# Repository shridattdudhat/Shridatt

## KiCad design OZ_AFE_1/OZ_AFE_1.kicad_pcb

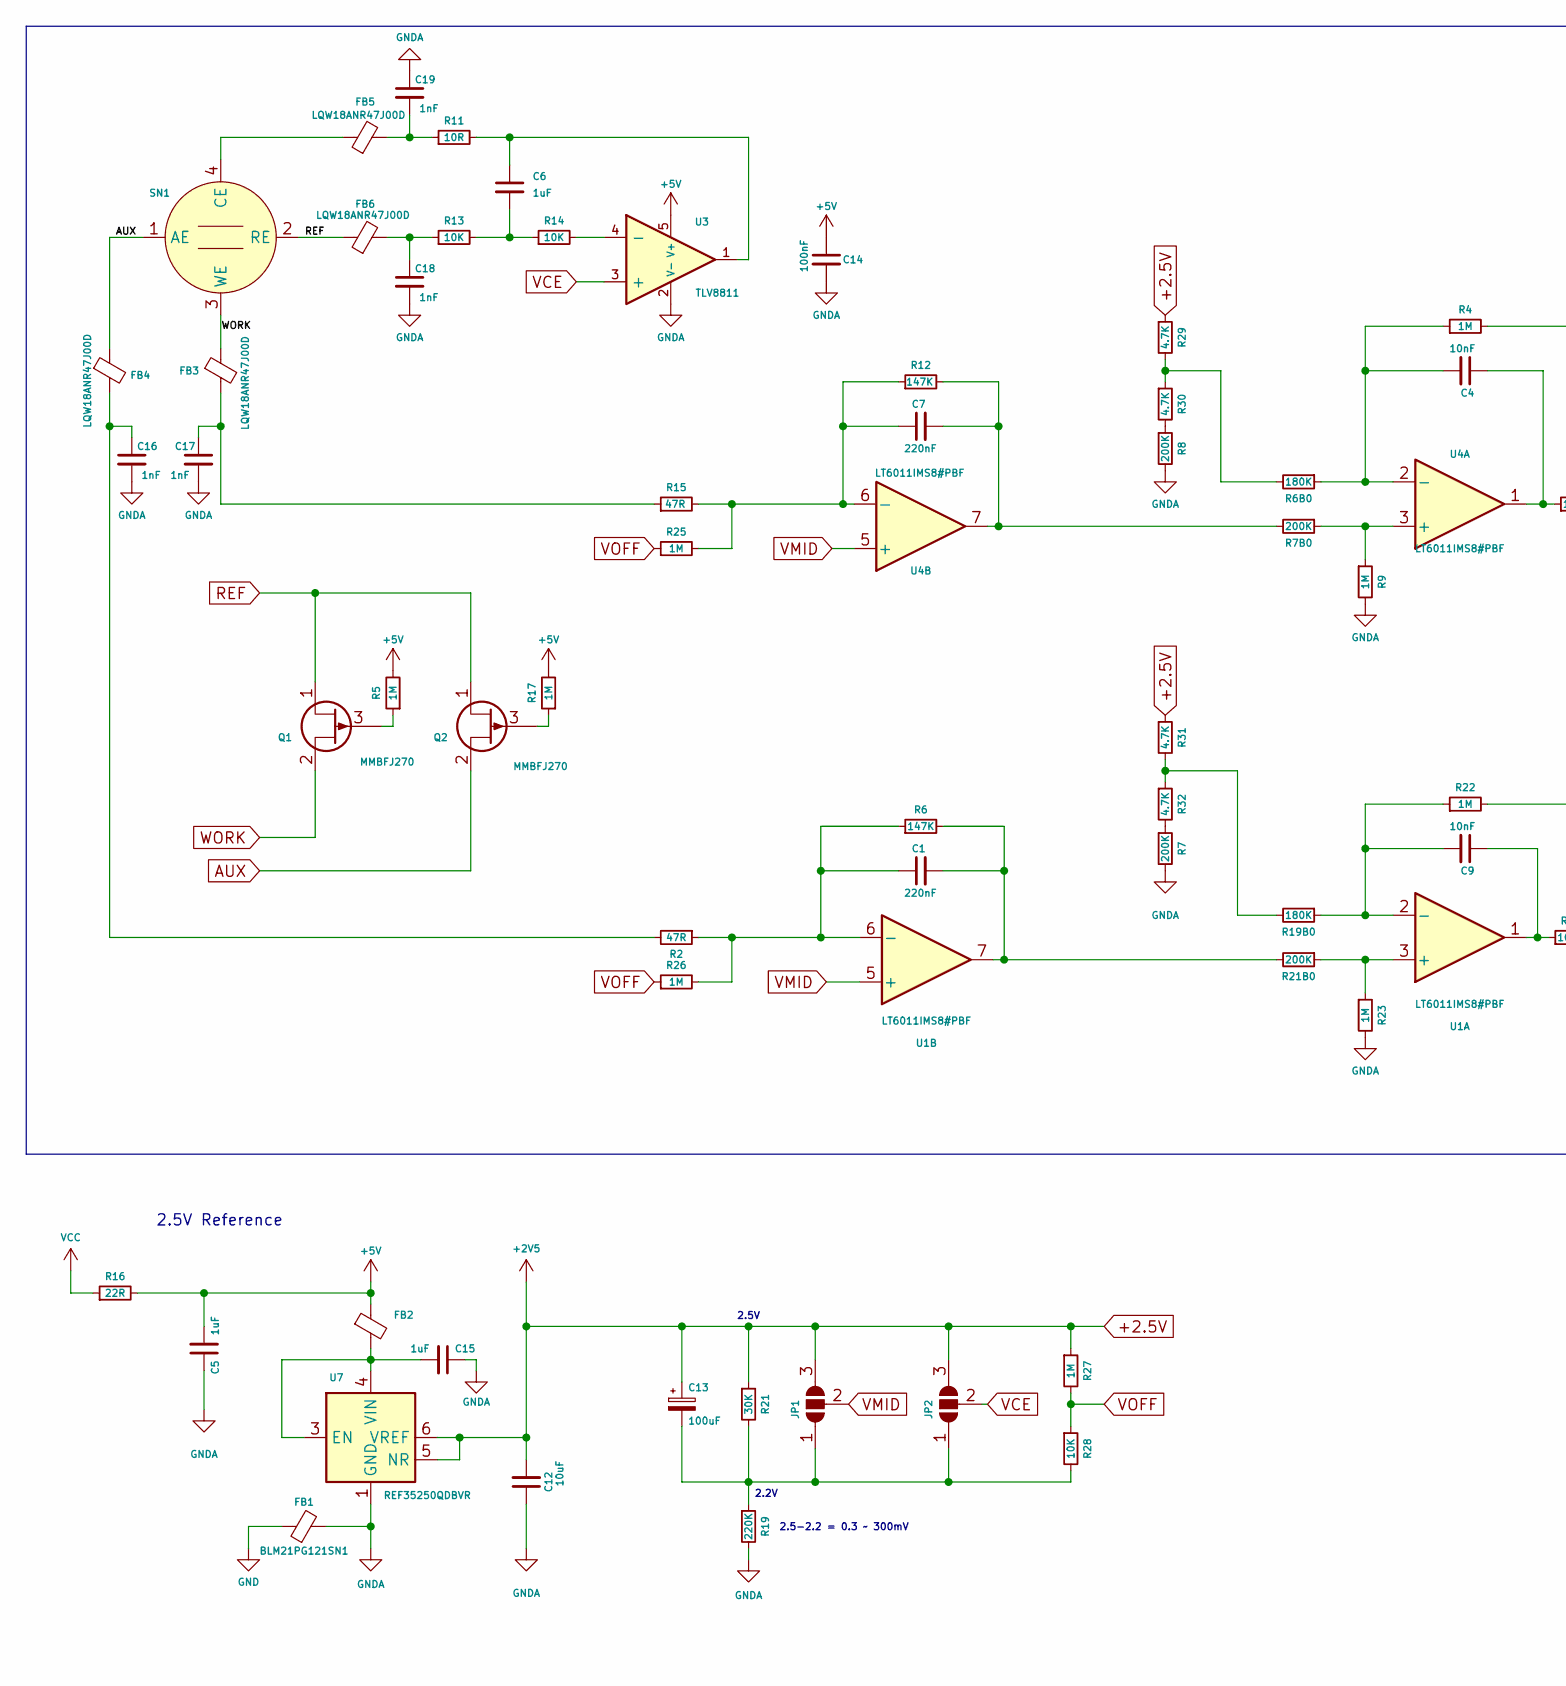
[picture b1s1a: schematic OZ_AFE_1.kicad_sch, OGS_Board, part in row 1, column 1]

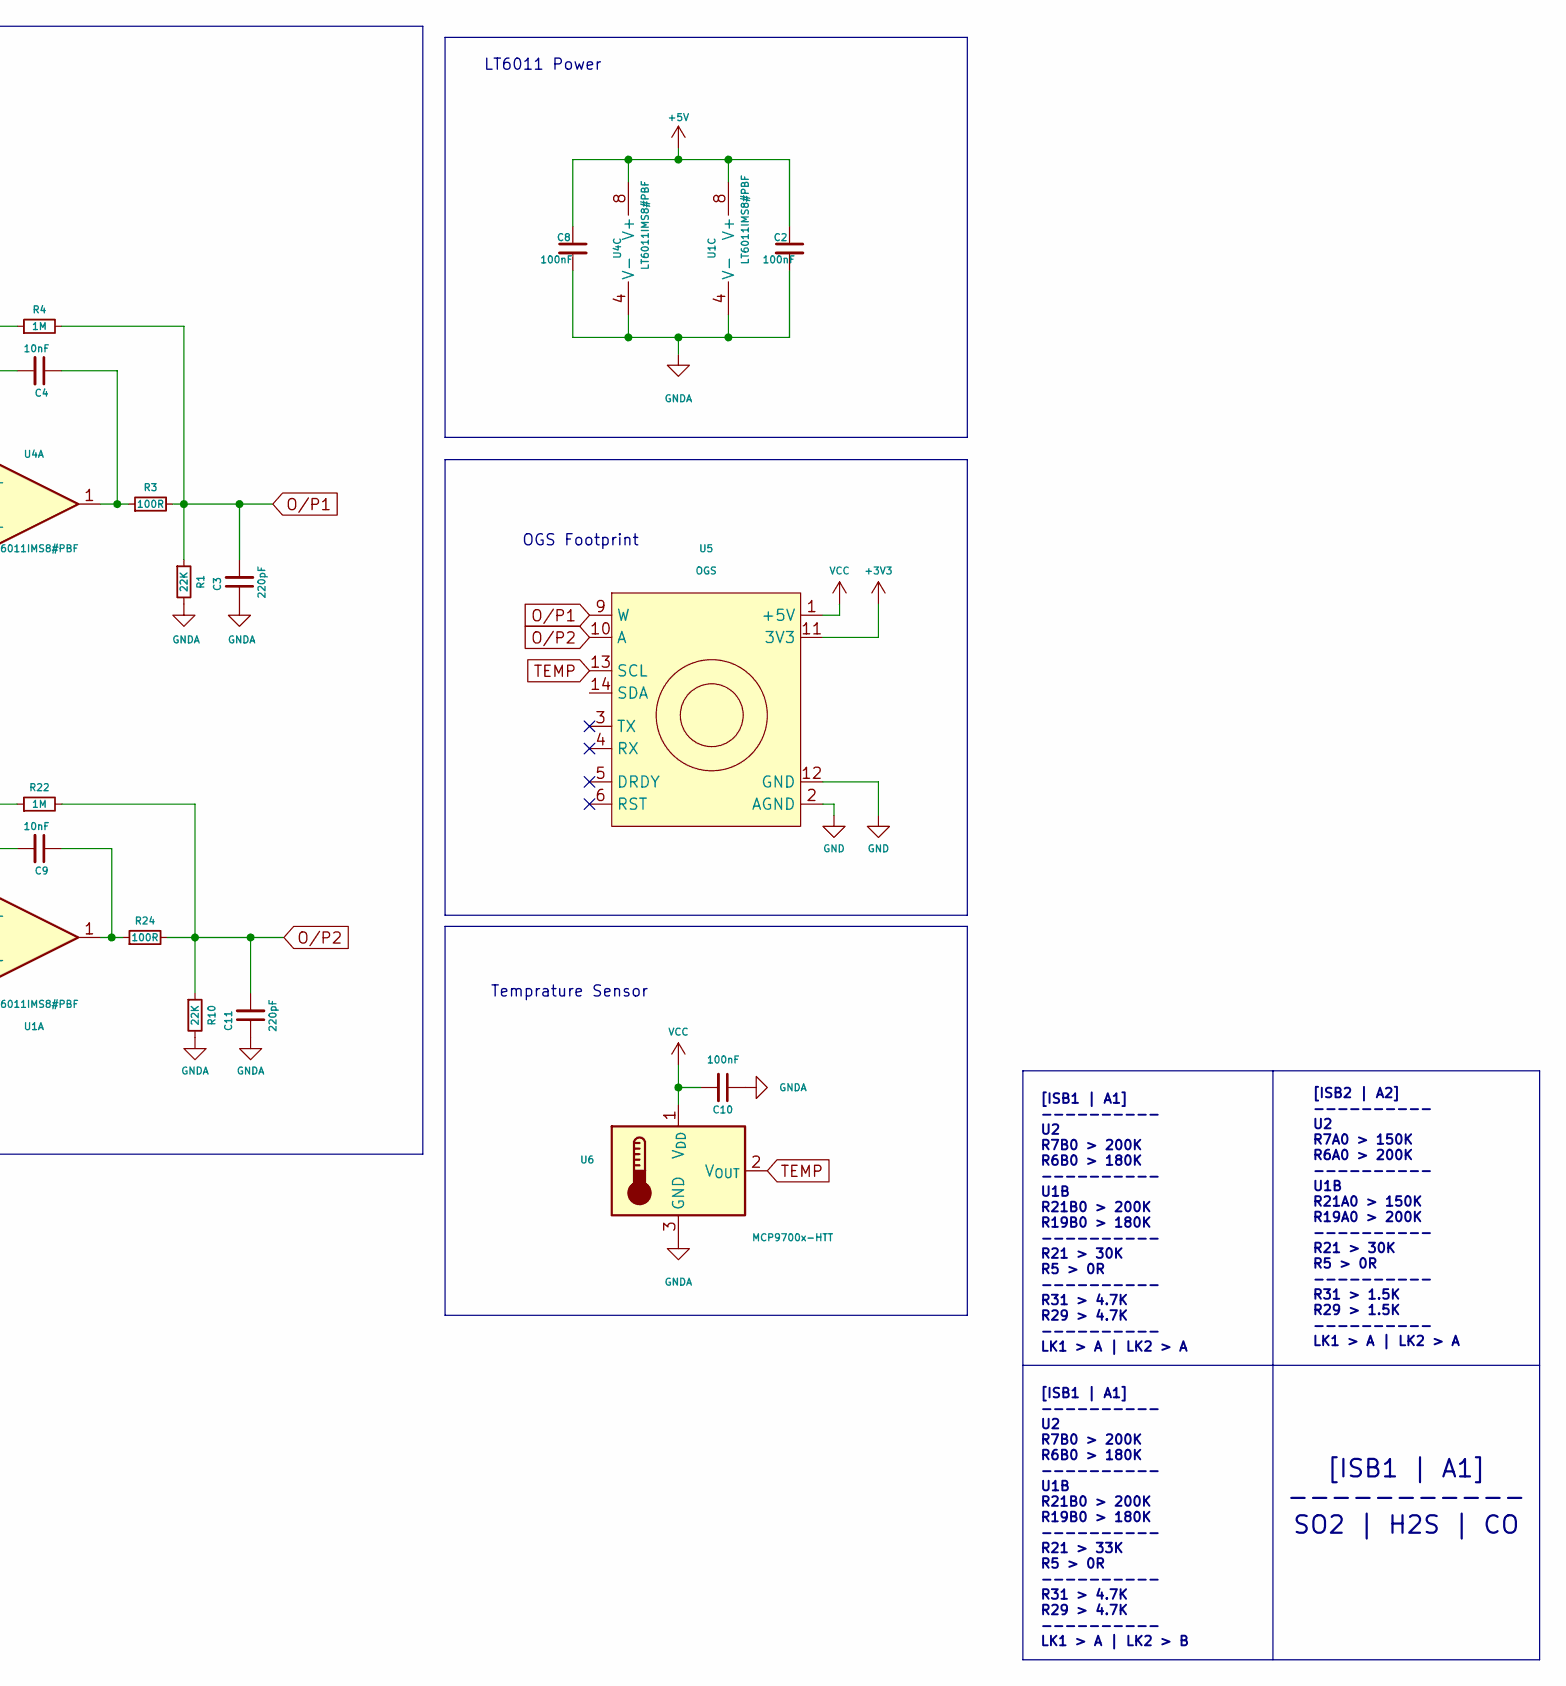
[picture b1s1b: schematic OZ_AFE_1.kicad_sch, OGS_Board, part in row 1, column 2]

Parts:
C1, C7: 220nF; C_0603_1608Metric
C2, C8, C10, C14: 100nF; C_0603_1608Metric
C3, C11: 220pF; C_0603_1608Metric
C4, C9: 10nF; C_0603_1608Metric
C5, C6, C15: 1uF; C_0603_1608Metric
C12: 10uF; C_0603_1608Metric
C13: 100uF; CP_EIA-3528-12_Kemet-T
C16, C17, C18, C19: 1nF; C_0402_1005Metric
FB1, FB2: BLM21PG121SN1; R_0805_2012Metric
FB3, FB4, FB5, FB6: LQW18ANR47J00D; L_0603_1608Metric
JP1, JP2: SolderJumper_3_Open; SolderJumper-3_P1.3mm_Open_RoundedPad1.0x1.5mm
Q1, Q2: MMBFJ270; SOT-23
R1, R10: 22K; R_0402_1005Metric
R2, R15: 47R; R_0402_1005Metric
R3, R24: 100R; R_0402_1005Metric
R4, R5, R9, R17, R22, R23, R25, R26, R27: 1M; R_0402_1005Metric
R6, R12: 147K; R_0603_1608Metric
R6B0, R19B0: 180K; R_0603_1608Metric
R7, R7B0, R8, R21B0: 200K; R_0603_1608Metric
R11: 10R; R_0603_1608Metric
R13, R14, R28: 10K; R_0402_1005Metric
R16: 22R; R_0603_1608Metric
R19: 220K; R_0603_1608Metric
R21: 30K; R_0603_1608Metric
R29, R30, R31, R32: 4.7K; R_0603_1608Metric
SN1: Alphasense-B4
U1, U4: LT6011IMS8#PBF; MSOP-8_3x3mm_P0.65mm
U3: TLV8811; SOT-23-6
U5: OGS; OGSB_2MM
U6: MCP9700x-HTT; SOT-23
U7: REF35250QDBVR; SOT-23-6

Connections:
+2.5V: C12.2, C13.1, JP1.3 (B), JP2.3 (B), R21.1, R27.1, R29.1, R31.1, U7.5 (NR), U7.6 (VREF)
+3V3: U5.11 (3V3)
+5V: C2.1, C5.2, C8.1, C14.1, FB2.1, R5.2, R16.2, R17.2, U1.8 (V+), U3.5 (V+), U4.8 (V+)
AUX: FB4.1, Q2.2 (S), SN1.1 (AE)
GND: FB1.1, U5.2 (AGND), U5.8 (GND), U5.12 (GND)
GNDA: C2.2, C3.1, C5.1, C8.2, C10.1, C11.1, C12.1, C14.2, C15.1, C16.2, C17.2, C18.2, C19.1, FB1.2, R1.2, R7.2, R8.2, R9.2, R10.2, R19.2, R23.2, U1.4 (V-), U3.2 (V-), U4.4 (V-), U6.3 (GND), U7.1 (GND), U7.2 (GND)
unnamed: C1.2, R6.2, R21B0.2, U1.7
unnamed: C4.1, R3.1, U4.1
unnamed: C6.1, R11.2, U3.1
unnamed: C6.2, R13.2, R14.1
unnamed: C7.2, R7B0.2, R12.2, U4.7
unnamed: C9.1, R24.1, U1.1
unnamed: C16.1, FB4.2, R2.2
unnamed: C17.1, FB3.2, R15.1
unnamed: C18.1, FB6.2, R13.1
unnamed: C19.2, FB5.2, R11.1
unnamed: C13.2, JP1.1 (A), JP2.1 (A), R19.1, R21.2, R28.2
unnamed: Q1.3 (G), R5.1
unnamed: Q2.3 (G), R17.1
unnamed: R19B0.2, R31.2, R32.1
unnamed: R6B0.2, R29.2, R30.1
unnamed: R8.1, R30.2
unnamed: R7.1, R32.2
unnamed: FB5.1, SN1.4 (CE)
unnamed: R21B0.1, R23.1, U1.3 (+)
unnamed: C9.2, R19B0.1, R22.1, U1.2 (-)
unnamed: C1.1, R2.1, R6.1, R26.2, U1.6 (-)
unnamed: R14.2, U3.4 (-)
unnamed: R7B0.1, R9.1, U4.3 (+)
unnamed: C4.2, R4.1, R6B0.1, U4.2 (-)
unnamed: C7.1, R12.1, R15.2, R25.2, U4.6 (-)
unnamed: C15.2, FB2.2, U7.3 (EN), U7.4 (VIN)
O/P1: C3.2, R1.1, R3.2, R4.2, U5.9 (W)
O/P2: C11.2, R10.1, R22.2, R24.2, U5.10 (A)
REF: FB6.1, Q1.1 (D), Q2.1 (D), SN1.2 (RE)
TEMP: U5.13 (SCL), U6.2 (V_{OUT})
VCC: C10.2, R16.1, U5.1 (+5V), U5.7 (+5V), U6.1 (V_{DD})
VCE: JP2.2 (C), U3.3 (+)
VMID: JP1.2 (C), U1.5 (+), U4.5 (+)
VOFF: R25.1, R26.1, R27.2, R28.1
WORK: FB3.1, Q1.2 (S), SN1.3 (WE)

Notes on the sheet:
OGS Footprint
Temprature Sensor
[ISB2 | A2] ---------- U2 R7A0 > 150K R6A0 > 200K ---------- U1B R21A0 > 150K R19A0 > 200K ---------- R21 > 30K R5 > 0R ---------- R31 > 1.5K R29 > 1.5K ---------- LK1 > A | LK2 > A
LT6011 Power
2.5V
[ISB1 | A1] ----------- SO2 | H2S | CO
2.2V
2.5V Reference
2.5-2.2 = 0.3 ~ 300mV
[ISB1 | A1] ---------- U2 R7B0 > 200K R6B0 > 180K ---------- U1B R21B0 > 200K R19B0 > 180K ---------- R21 > 30K R5 > 0R ---------- R31 > 4.7K R29 > 4.7K ---------- LK1 > A | LK2 > A
[ISB1 | A1] ---------- U2 R7B0 > 200K R6B0 > 180K ---------- U1B R21B0 > 200K R19B0 > 180K ---------- R21 > 33K R5 > 0R ---------- R31 > 4.7K R29 > 4.7K ---------- LK1 > A | LK2 > B

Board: 2 copper layers, 70 parts (4 on the bottom side), 40 nets, no tracks yet.

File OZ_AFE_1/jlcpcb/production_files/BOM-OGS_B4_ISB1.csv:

Comment,Designator,Footprint,LCSC
100uF,C13,CP_EIA-3528-12_Kemet-T,C122644
BZV55-C6V8,D1,D_MiniMELF,C128833
100nF,"C10,C8",C_0603_1608Metric,C14663
1uF,"C5,C6",C_0603_1608Metric,C15849
220pF,"C11,C3",C_0603_1608Metric,C1603
10uF,"C12,C2",C_0603_1608Metric,C19702
220nF,"C1,C7",C_0603_1608Metric,C21120
0R,"R5A0,R5B0",R_0603_1608Metric,C21189
100R,"R24,R3",R_0603_1608Metric,C22775
180K,"R19B0,R6B0",R_0603_1608Metric,C22827
10R,R11,R_0603_1608Metric,C22859
1M,"R22,R23,R25,R26,R27,R4,R9",R_0603_1608Metric,C22935
220K,R19,R_0603_1608Metric,C22961
30K,R21,R_0603_1608Metric,C22984
4.7K,"R29,R30,R31,R32",R_0603_1608Metric,C23162
47R,"R15,R2",R_0603_1608Metric,C23182
22R,R16,R_0603_1608Metric,C23345
100K,"R12,R6",R_0603_1608Metric,C25803
10K,"R13,R14,R28",R_0603_1608Metric,C25804
200K,"R21B0,R7,R7B0,R8",R_0603_1608Metric,C25811
47K,"R17,R18",R_0603_1608Metric,C25819
22K,"R1,R10",R_0603_1608Metric,C31850
ISL21009BFB825Z,U3,SOIC-8_3.9x4.9mm_P1.27mm,C403914
TLV2211,U2,SOT-23-5,C50325
10nF,"C4,C9",C_0603_1608Metric,C57112
LT6011,"U1,U4",SOIC-8_3.9x4.9mm_P1.27mm,C672729
DNP,R7A0,R_0603_1608Metric,
N/F,R20,R_0603_1608Metric,
DNP,R6A0,R_0603_1608Metric,
DNP,R21A0,R_0603_1608Metric,
DNP,R19A0,R_0603_1608Metric,
OGS,U5,OGSB_2MM,
~,SN1,Alphasense-B4,
MCP9700x-HTT,U6,SOT-23,

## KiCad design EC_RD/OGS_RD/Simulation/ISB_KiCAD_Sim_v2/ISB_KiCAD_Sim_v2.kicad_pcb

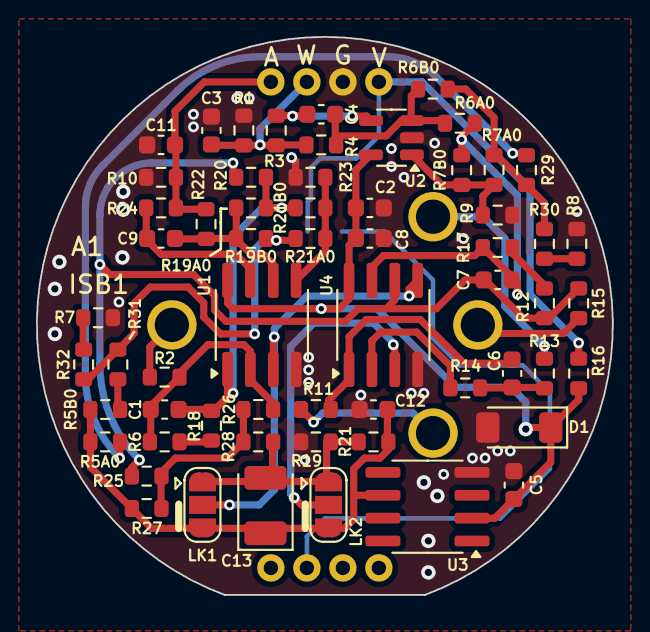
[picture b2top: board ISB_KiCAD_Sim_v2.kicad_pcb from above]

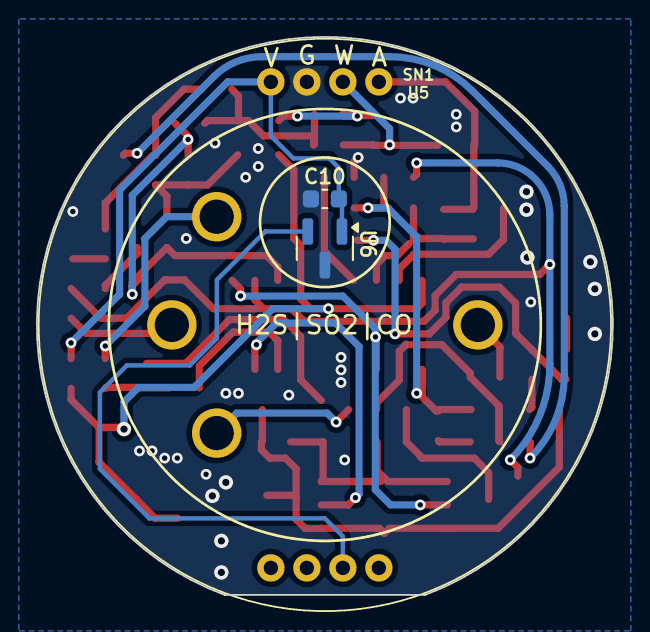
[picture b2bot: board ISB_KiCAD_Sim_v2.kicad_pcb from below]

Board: 2 copper layers, 32.0 x 31.0 mm, 64 parts (4 on the bottom side), 36 nets.

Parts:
C1, C7: 220nF; C_0603_1608Metric
C2, C12: 10uF; C_0603_1608Metric
C3, C11: 220pF; C_0603_1608Metric
C4, C9: 10nF; C_0603_1608Metric
C5, C6: 1uF; C_0603_1608Metric
C8, C10: 100nF; C_0603_1608Metric
C13: 100uF; CP_EIA-3528-12_Kemet-T
D1: BZV55-C6V8; D_MiniMELF
LK1: LK1; SolderJumper-3_P1.3mm_Open_RoundedPad1.0x1.5mm
LK2: LK2; SolderJumper-3_P1.3mm_Open_RoundedPad1.0x1.5mm
R1, R10: 22K; R_0603_1608Metric
R2, R15: 47R; R_0603_1608Metric
R3, R24: 100R; R_0603_1608Metric
R4, R9, R22, R23, R25, R26, R27: 1M; R_0603_1608Metric
R5A0, R5B0: 0R; R_0603_1608Metric
R6, R12: 100K; R_0603_1608Metric
R6A0, R7A0, R19A0, R21A0: DNP; R_0603_1608Metric
R6B0, R19B0: 180K; R_0603_1608Metric
R7, R7B0, R8, R21B0: 200K; R_0603_1608Metric
R11: 10R; R_0603_1608Metric
R13, R14, R28: 10K; R_0603_1608Metric
R16: 22R; R_0603_1608Metric
R17, R18: 47K; R_0603_1608Metric
R19: 220K; R_0603_1608Metric
R20: N/F; R_0603_1608Metric
R21: 30K; R_0603_1608Metric
R29, R30, R31, R32: 4.7K; R_0603_1608Metric
SN1: Alphasense-B4
U1, U4: LT6011; SOIC-8_3.9x4.9mm_P1.27mm
U2: TLV2211; SOT-23-5
U3: ISL21009BFB825Z; SOIC-8_3.9x4.9mm_P1.27mm
U5: OGS; OGSB_2MM
U6: MCP9700x-HTT; SOT-23

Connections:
+6V: C2.1, C5.2, C8.1, D1.1 (K), R16.2, U1.8 (V+), U2.5 (V+), U3.2 (Vin), U4.8 (V+)
GNDA: C2.2, C3.1, C5.1, C8.2, C10.1, C11.1, C12.1, D1.2 (A), R1.2, R7.2, R8.2, R9.2, R10.2, R19.2, R23.2, U1.4 (V-), U2.2 (V-), U3.4 (GND), U4.4 (V-), U5.8 (GND), U6.3 (GND)
unnamed: C1.2, R18.1, R19A0.2, R20.1, R21B0.2, U1.1
unnamed: C4.1, R3.1, U2.4
unnamed: C6.1, R11.2, U4.1
unnamed: C6.2, R13.2, R14.1
unnamed: C7.2, R6A0.2, R7B0.2, R17.1, U4.7
unnamed: C9.1, R24.1, U1.7
unnamed: C13.2, LK1.1 (A), LK2.1 (A), R19.1, R21.2, R28.2
unnamed: C12.2, C13.1, LK1.3 (B), LK2.3 (B), R5A0.1, R5B0.1, R21.1, R27.1, U3.6 (Vout)
unnamed: R12.2, R17.2
unnamed: R6.2, R18.2
unnamed: R19B0.2, R21A0.2, R31.2, R32.1
unnamed: R6B0.2, R7A0.2, R29.2, R30.1
unnamed: R8.1, R30.2
unnamed: R7.1, R32.2
unnamed: R2.2, SN1.1 (AE)
unnamed: R11.1, SN1.4 (CE)
unnamed: R13.1, SN1.2 (RE)
unnamed: R15.1, SN1.3 (WE)
unnamed: C1.1, R2.1, R6.1, R26.2, U1.2 (-)
unnamed: R21A0.1, R21B0.1, R23.1, U1.5 (+)
unnamed: C9.2, R19A0.1, R19B0.1, R22.1, U1.6 (-)
unnamed: R7A0.1, R7B0.1, R9.1, U2.1 (+)
unnamed: C4.2, R4.1, R6A0.1, R6B0.1, U2.3 (-)
unnamed: R14.2, U4.2 (-)
unnamed: C7.1, R12.1, R15.2, R20.2, R25.2, U4.6 (-)
O/P1: C3.2, R1.1, R3.2, R4.2, U5.9 (W)
O/P2: C11.2, R10.1, R22.2, R24.2, U5.10 (A)
TEMP: U5.13 (SCL), U6.2 (V_{OUT})
VCC: C10.2, R16.1, U5.7 (+5V), U6.1 (V_{DD})
VCE: LK2.2 (C), U4.3 (+)
VMID: LK1.2 (C), U1.3 (+), U4.5 (+)
VOFF: R25.1, R26.1, R27.2, R28.1
VPOT1: R5A0.2, R29.1
VPOT2: R5B0.2, R31.1

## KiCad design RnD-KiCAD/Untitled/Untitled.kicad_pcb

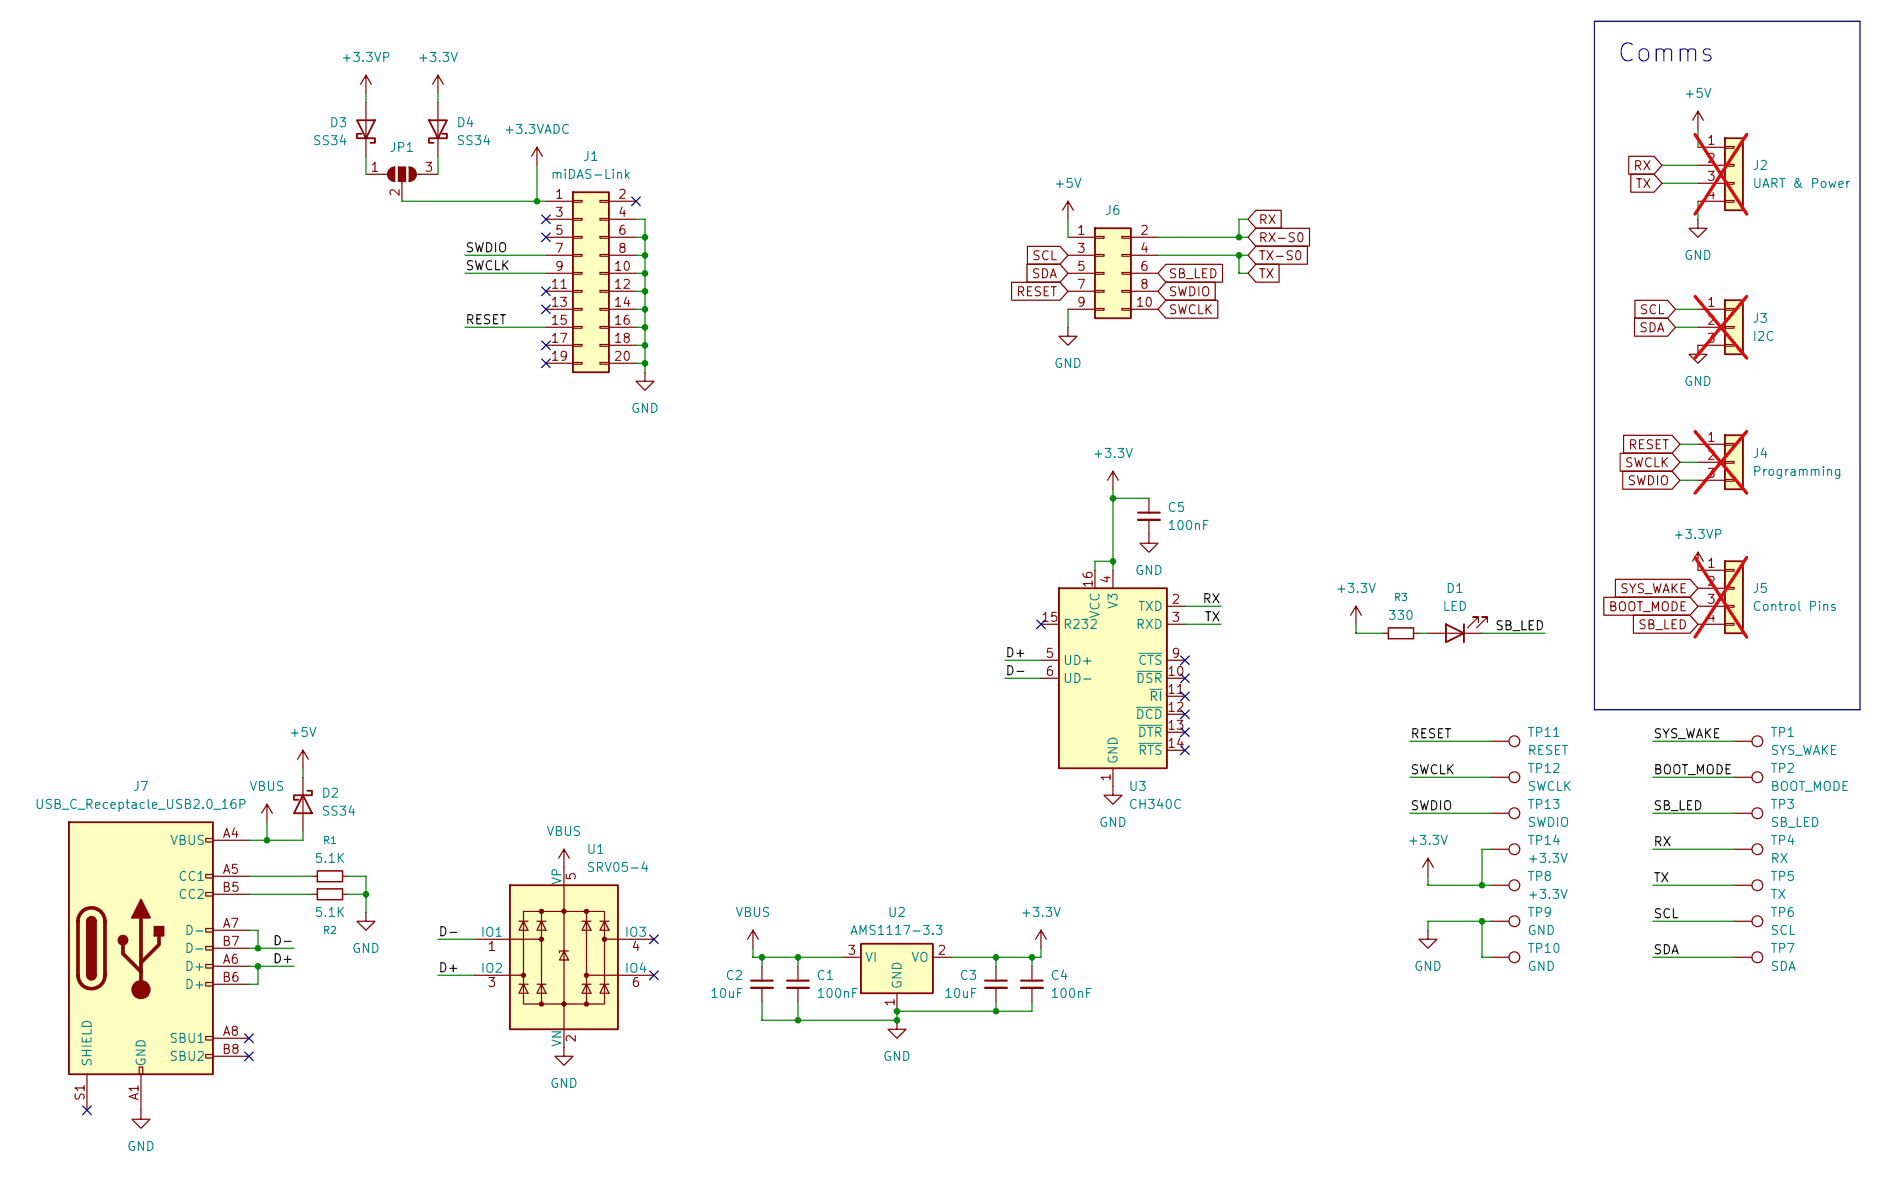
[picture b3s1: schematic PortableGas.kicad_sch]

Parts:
C1, C4, C5: 100nF; C_0603_1608Metric_Pad1.08x0.95mm_HandSolder
C2, C3: 10uF; C_0603_1608Metric_Pad1.08x0.95mm_HandSolder
D1: LED; LED_0603_1608Metric_Pad1.05x0.95mm_HandSolder
D2, D3, D4: SS34; D_SMA
J1: miDAS-Link; IDC-Header_2x10_P2.54mm_Vertical
J2: UART & Power; PinSocket_1x04_P2.00mm_Vertical; not fitted
J3: I2C; PinSocket_1x03_P2.00mm_Vertical; not fitted
J4: Programming; PinSocket_1x03_P2.00mm_Vertical; not fitted
J5: Control Pins; PinSocket_1x04_P2.00mm_Vertical; not fitted
J6: Conn_02x05_Odd_Even; PinSocket_2x05_P2.54mm_Vertical-idc
J7: USB_C_Receptacle_USB2.0_16P; USB_C_Receptacle_G-Switch_GT-USB-7010ASV
JP1: SolderJumper_3_Open; SolderJumper-3_P1.3mm_Open_RoundedPad1.0x1.5mm
R1, R2: 5.1K; R_0603_1608Metric_Pad0.98x0.95mm_HandSolder
R3: 330; R_0603_1608Metric_Pad0.98x0.95mm_HandSolder
TP1: SYS_WAKE; TestPoint_THTPad_D2.0mm_Drill1.0mm
TP2: BOOT_MODE; TestPoint_THTPad_D2.0mm_Drill1.0mm
TP3: SB_LED; TestPoint_THTPad_D2.0mm_Drill1.0mm
TP4: RX; TestPoint_THTPad_D2.0mm_Drill1.0mm
TP5: TX; TestPoint_THTPad_D2.0mm_Drill1.0mm
TP6: SCL; TestPoint_THTPad_D2.0mm_Drill1.0mm
TP7: SDA; TestPoint_THTPad_D2.0mm_Drill1.0mm
TP8, TP14: +3.3V; TestPoint_THTPad_D2.0mm_Drill1.0mm
TP9, TP10: GND; TestPoint_THTPad_D2.0mm_Drill1.0mm
TP11: RESET; TestPoint_THTPad_D2.0mm_Drill1.0mm
TP12: SWCLK; TestPoint_THTPad_D2.0mm_Drill1.0mm
TP13: SWDIO; TestPoint_THTPad_D2.0mm_Drill1.0mm
U1: SRV05-4; SOT-23-6_Handsoldering
U2: AMS1117-3.3; SOT-223-3_TabPin2
U3: CH340C; SOIC-16_3.9x9.9mm_P1.27mm

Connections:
+3.3V: C3.1, C4.1, C5.1, D4.2 (A), R3.1, TP8.1, TP14.1, U2.2 (VO), U3.4 (V3), U3.16 (VCC)
+3.3VADC: J1.1, JP1.2 (C)
+3.3VP: D3.2 (A), J5.1
+5V: D2.1 (K), J2.1, J6.1
/D+: J7.A6 (D+), J7.B6 (D+), U1.3 (IO2), U3.5 (UD+)
/D-: J7.A7 (D-), J7.B7 (D-), U1.1 (IO1), U3.6 (UD-)
BOOT_MODE: J5.3, TP2.1
GND: C1.2, C2.2, C3.2, C4.2, C5.2, J1.4, J1.6, J1.8, J1.10, J1.12, J1.14, J1.16, J1.18, J1.20, J2.4, J3.3, J6.9, J7.A1 (GND), J7.A12 (GND), J7.B1 (GND), J7.B12 (GND), R1.2, R2.2, TP9.1, TP10.1, U1.2 (VN), U2.1 (GND), U3.1 (GND)
unnamed: D1.2 (A), R3.2
unnamed: D3.1 (K), JP1.1 (A)
unnamed: D4.1 (K), JP1.3 (B)
unnamed: J7.A5 (CC1), R1.1
unnamed: J7.B5 (CC2), R2.1
RESET: J1.15, J4.1, J6.7, TP11.1
RX: J2.2, J6.2, TP4.1, U3.2 (TXD)
SB_LED: D1.1 (K), J5.4, J6.6, TP3.1
SCL: J3.1, J6.3, TP6.1
SDA: J3.2, J6.5, TP7.1
SWCLK: J1.9, J4.2, J6.10, TP12.1
SWDIO: J1.7, J4.3, J6.8, TP13.1
SYS_WAKE: J5.2, TP1.1
TX: J2.3, J6.4, TP5.1, U3.3 (RXD)
VBUS: C1.1, C2.1, D2.2 (A), J7.A4 (VBUS), J7.A9 (VBUS), J7.B4 (VBUS), J7.B9 (VBUS), U1.5 (VP), U2.3 (VI)

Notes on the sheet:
Comms

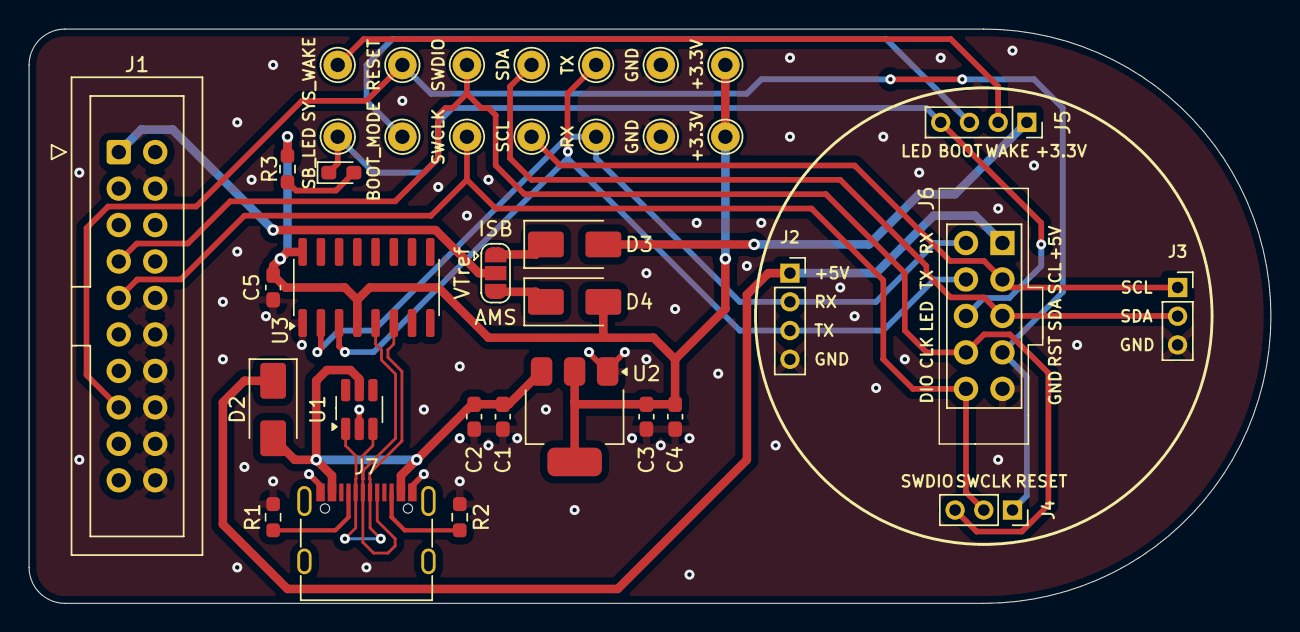
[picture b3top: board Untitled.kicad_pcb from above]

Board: 2 copper layers, 86.5 x 40.0 mm, 37 parts (0 on the bottom side), 23 nets.

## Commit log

2025-08-24 kicad project
2025-08-24 OZ_AFE
2025-08-24 clean
2025-08-24 EC_RD commit
2025-08-25 New Simulation and PCB
2025-09-13 sch update
